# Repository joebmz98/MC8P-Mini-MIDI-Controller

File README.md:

# MC8P Mini MIDI Controller

---

# **8-Pot Mini MIDI Controller**

A compact, open-source MIDI controller with **8 potentiometers**, each with **fully assignable MIDI CCs**, built for **Arduino NANO R3/R4 (Rev1)** or the **Pro Micro (Rev2)**.

---

## **Features**
- **8x Potentiometers** with smooth analog control via 16-channel MUX
- **Arduino NANO / Pro Micro (Rev2) Compatible** – Easy to source and program
- **SSD1306 I2C OLED (128x64)** for the UI
- **Per-Pot CC Assignment** – Full MIDI CC customization
- **4x Tactile Switches** for UI navigation/configuration
- **Standalone Operation** – No computer needed after setup
- **EEPROM Settings Storage** – Retains configurations after power-off
- **Temporary Override Mode** – Make temporary adjustments that snap back
- **MIDI over USB** (Pro Micro Rev ONLY) – Class-compliant, plug-and-play
- **Open-Source Firmware** (Arduino IDE-compatible)

---

## **Bill of Materials (BOM)**

| Component                  | Qty | Notes                          | Links / Part Numbers |
|----------------------------|-----|--------------------------------|----------------------|
| Arduino NANO / Pro Micro   | 1   | Main microcontroller           | [Arduino NANO R3](https://www.aliexpress.com/w/wholesale-arduino-nano.html?spm=a2g0o.productlist.search.0) / [Pro Micro](https://www.aliexpress.com/w/wholesale-pro-micro-arduino.html?spm=a2g0o.best.search.0) |
| 16-Channel MUX (74HC4067)  | 1   | For reading 8 potentiometers   | [AliExpress](https://www.aliexpress.com/w/wholesale-cd74hc4067.html?spm=a2g0o.productlist.search.0) / CD74HC4067M96 (JLCPCB) |
| SSD1306 OLED (128×64)      | 1   | I²C interface                  | [AliExpress](https://www.aliexpress.com/w/wholesale-ssd1306.html?spm=a2g0o.productlist.search.0) |
| B100K Potentiometers       | 8   | Linear taper                   | [AliExpress](https://www.aliexpress.com/item/1005003523799166.html?spm=a2g0o.productlist.main.4.41b16412N16EC4&aem_p4p_detail=2026050202175910656752474918880005794025&algo_pvid=bb6ca2a0-bb84-4b86-8104-57e7c6a92d56&algo_exp_id=bb6ca2a0-bb84-4b86-8104-57e7c6a92d56-3&pdp_ext_f=%7B"order"%3A"368"%2C"eval"%3A"1"%2C"fromPage"%3A"search"%7D&pdp_npi=6%40dis%21GBP%210.33%210.33%21%21%210.43%210.43%21%402151e6dc17777134792648341e4c8f%2112000026166615223%21sea%21UK%216042796089%21X%211%210%21n_tag%3A-29919%3Bd%3A582ad943%3Bm03_new_user%3A-29895&curPageLogUid=hZYrDWLC06u8&utparam-url=scene%3Asearch%7Cquery_from%3A%7Cx_object_id%3A1005003523799166%7C_p_origin_prod%3A&search_p4p_id=2026050202175910656752474918880005794025_1) |
| Tactile Switches           | 4   | For menu navigation (ASSIGN, ENTER, PREV, NEXT) | K2-6639DP-B4SW-04 (JLCPCB) |
| 10k Resistors (SMD)        | 7   | Button pull-downs (R3–R6), MUX enable pull-down (R7), MIDI jumpers (R8, R9) | 0603WAF1002T5E (JLCPCB) |
| 100nF SMD Capacitor        | 1   | Power rail stabilisation       | 1206B104K101CT (JLCPCB) |
| 10nF SMD Capacitors        | 8   | Potentiometer filtering        | 1206B103K500NT (JLCPCB) |
| 220Ω SMD Resistors         | 2   | For MIDI circuitry             | 0603WAF2200T5E (JLCPCB) |
| PJ307 Stereo Headphone Socket | 1 | 3.5mm MIDI TRS Out (Type A) | — |
| Reset Button (SMD)         | 1   | Rev2 only - Reset button       | KMR221GLFS (JLCPCB) |
| 0.1" Header Pins           | 1   | For connecting components      | — |
| PCB                        | 1   | Custom design                  | — |
| Potentiometer Knobs        | 8   | For B100K potentiometers       | — |

---

## **Available Purchase Options**
**DIY Kits** - Only NANO version (rev1) available → [**Purchase from my Tindie store**](https://www.tindie.com/stores/axsinstruments/)

---

## **Installation & Setup**
### **1. Flashing the Firmware**
- Install **Arduino IDE**
- Install required libraries (see Building from Source section)
- Open the `.ino` file in Arduino IDE | There are two files - one for NANO and one for Pro Micro
- Select your board (**Arduino NANO R3/R4 or ProMicro**)
- Upload the firmware

### **2. Hardware Assembly**
- Refer to the *Build Guide* (coming soon)

### **3. First Boot**
- Power via **USB** on the Arduino NANO
- Use the **OLED menu** to assign CCs

---

## **Configuration**

### Button Functions

| Button | Primary Function |
|--------|-----------------|
| ASSIGN | Enter/exit MIDI assignment menu |
| ENTER | Enter temporary override mode (hold), confirm selections |
| PREV | Decrease values, navigate up |
| NEXT | Increase values, navigate down |
| PREV + NEXT (hold 2 sec) | Factory reset |

### Screen Hierarchy

The interface is organized into two main screens:

**MAIN SCREEN** → **ASSIGN SCREEN** → parameter editing

### Main Screen

This is your default operating view. The screen displays:
- Current selected pot number (1-8)
- A horizontal bar graph showing the current MIDI value (0-127)
- The numeric MIDI value centered on screen

From the main screen:
- Press **ASSIGN** to enter the assign menu
- Press and hold **ENTER** to activate temporary override mode

### Temporary Override Mode

When you press and hold ENTER on the main screen, the controller enters temporary override mode:
- The display inverts as visual feedback
- All potentiometer adjustments override the stored values
- When you release ENTER, the controller:
  - Returns to the stored MIDI values
  - Activates catch-up mode
  - The display returns to normal

### Catch-Up Mode

After exiting temporary override mode, catch-up mode is activated:
- Potentiometers must pass through their stored position before taking control
- This prevents abrupt jumps in your MIDI parameters
- Each pot is caught up on its own – a pot only needs to reach or cross its stored value, and pots you didn't touch stay live (NANO firmware v1.1)

### Assign Screen (MIDI ASSIGN)

Press ASSIGN from the main screen to enter the configuration menu. Press ENTER to step through the edit modes:

**Navigation flow:**
1. **SELECT POT** – Choose which pot (1-8) to configure
2. **EDIT CHANNEL** – Set MIDI channel (1-16) or OMNI
3. **EDIT CC** – Set Control Change number (0-127)
4. **EDIT MIN** – Minimum output value (0-127)
5. **EDIT MAX** – Maximum output value (0-127)
6. **EDIT DIR** – Normal (0-127) or Inverted (127-0)

**Editing values:**
- **PREV/NEXT** – Adjust values incrementally
- **Potentiometer 8** – Smooth continuous adjustment across full range - faster when selecting MIDI CC's and custom ranges. It only takes over once you turn it, so entering a mode doesn't overwrite the current value (NANO firmware v1.1)
- **ENTER** – Cycle through edit modes
- **ASSIGN** – Save settings and return to main screen

### Factory Reset

From the main screen, press and hold **PREV + NEXT** for 2 seconds:
- All settings reset to defaults
- Device confirms reset on screen
- Resets to:
  - Channel 1-8 (one per pot)
  - CC 7 for all pots
  - Min 0, Max 127
  - Normal direction

---

## **MIDI Implementation**
- **USB MIDI** – Class-compliant in rev2, no drivers needed
- **Per-Pot Configuration** – Each pot has independent:
  - MIDI Channel (1-16 or OMNI)
  - CC Number (0-127)
  - Value Range (min/max 0-127)
  - Direction (Normal/Inverted)
- **EEPROM Storage** – Settings persist after power-off

---

## **Building from Source**
- Requires **Arduino IDE**
- Libraries:
  - `Adafruit_SSD1306` – OLED display driver
  - `Adafruit_GFX` – Graphics library for UI
  - `MIDI` – MIDI protocol handling
  - `EEPROM` – Settings storage (built-in)
- NANO R3: Arduino AVR Boards core **1.8.3 or newer** (needed for the I2C bus timeout that stops a glitched OLED bus from freezing the controller)
- NANO firmware v1.1 shows the free RAM in the top-left of the boot screen. Below ~250 bytes the NANO is at risk of stack overflow – the OLED buffer alone takes 1 KB of its 2 KB

### **Simulating in Wokwi**
- Set `#define WOKWI 1` at the top of the NANO firmware before simulating. Wokwi's CD74HC4067 model takes up to a couple of milliseconds to follow a channel change, so with the normal 20 µs settle time every pot appears to move with whichever pot you turn. Set it back to `0` for real hardware.
- Wire each button as on the PCB: one side to 5V, the other to the input pin with a 10k resistor to GND.
- Tie the MUX `EN` pin to GND.
- The serial monitor shows raw MIDI bytes, not text – e.g. `°` `±` `²` are 0xB0–0xB2, Control Change on channels 1–3.

---

## **Hardware Pin Connections**

| Component      | Arduino NANO (Rev1) | Pro Micro (Rev2) |
|----------------|---------------------|------------------|
| MUX SIG        | A0                  | A0               |
| MUX S0         | D6                  | D8               |
| MUX S1         | D7                  | D9               |
| MUX S2         | D8                  | D10              |
| MUX S3         | D9                  | D16              |
| ASSIGN Button  | D2                  | D4               |
| ENTER Button   | D3                  | D5               |
| PREV Button    | D4                  | D6               |
| NEXT Button    | D5                  | D7               |
| OLED SDA       | A4 (SDA)            | D2 (SDA)         |
| OLED SCL       | A5 (SCL)            | D3 (SCL)         |
| MIDI TRS Out   | D1 (TX)             | D1 (TX)          |
| Pot 1-8        | MUX Channels 0-7    | MUX Channels 0-7 |

**Buttons are active-HIGH.** Each switch connects its pin to 5V, with a 10k pull-down to GND (R3–R6), so a pin reads **HIGH when pressed** and LOW when released. Use `INPUT`, not `INPUT_PULLUP` – the internal pull-up fights the external pull-down and leaves the idle level around 0.8–1.7 V, right at the AVR's LOW threshold. NANO firmware v1.1 uses `INPUT`; the Pro Micro firmware (v1.0) still enables the pull-up.

---

## **Differences from MC8P**

| Feature           | MC8P (Teensy 4.0)    | MC8P mini (Arduino)      |
|-------------------|----------------------|---------------------------|
| Microcontroller   | Teensy 4.0           | Arduino NANO / Pro Micro  |
| MIDI Output       | USB + TRS 3.5mm      | Rev1 TRS Only / Rev2 USB + TRS 3.5mm |
| Max CCs per Pot   | Up to 10             | 1                         |
| EEPROM            | Yes                  | Yes                       |
| Catch-up Mode     | Yes                  | Yes                       |
| Temp Override     | Yes                  | Yes                       |

---

## **License**
**MIT License** – Open-source for personal & commercial use

---

## **Support & Contributions**
- **Issues:** Open a GitHub ticket
- **Custom Requests:** Start a thread in the discussions page or email: axs.instruments@gmail.com
- **Want to improve it?** PRs welcome!

---

## **Version History**
- **v1.1** (NANO firmware) – Stability & performance
  - Fixes freezes: I2C bus timeout with automatic OLED recovery
  - Catch-up is per pot – no more pots locking up after temp mode, or MIDI/OLED flooding while waiting
  - OLED redraws batched and capped at ~25 fps (each redraw is a full 1 KB I2C transfer)
  - Full 0–127 resolution with no jitter (raw-domain hysteresis replaces the change-of-2 threshold)
  - Per-button debounce; buttons read as active-HIGH with `INPUT` to match the board's pull-downs
  - Faster ADC reads, ~120 bytes RAM saved from the MIDI library, free RAM on the boot screen
  - NANO R3 / R4 detected automatically – no lines to comment in/out
  - EEPROM layout unchanged – saved settings are kept when updating from v1.0
- **v1.0** – Initial release
  - 8-pot control via 74HC4067 MUX
  - Full MIDI CC assignment per pot
  - OLED UI with assign menu
  - EEPROM settings storage
  - Temporary override and catch-up modes
  - Factory reset function

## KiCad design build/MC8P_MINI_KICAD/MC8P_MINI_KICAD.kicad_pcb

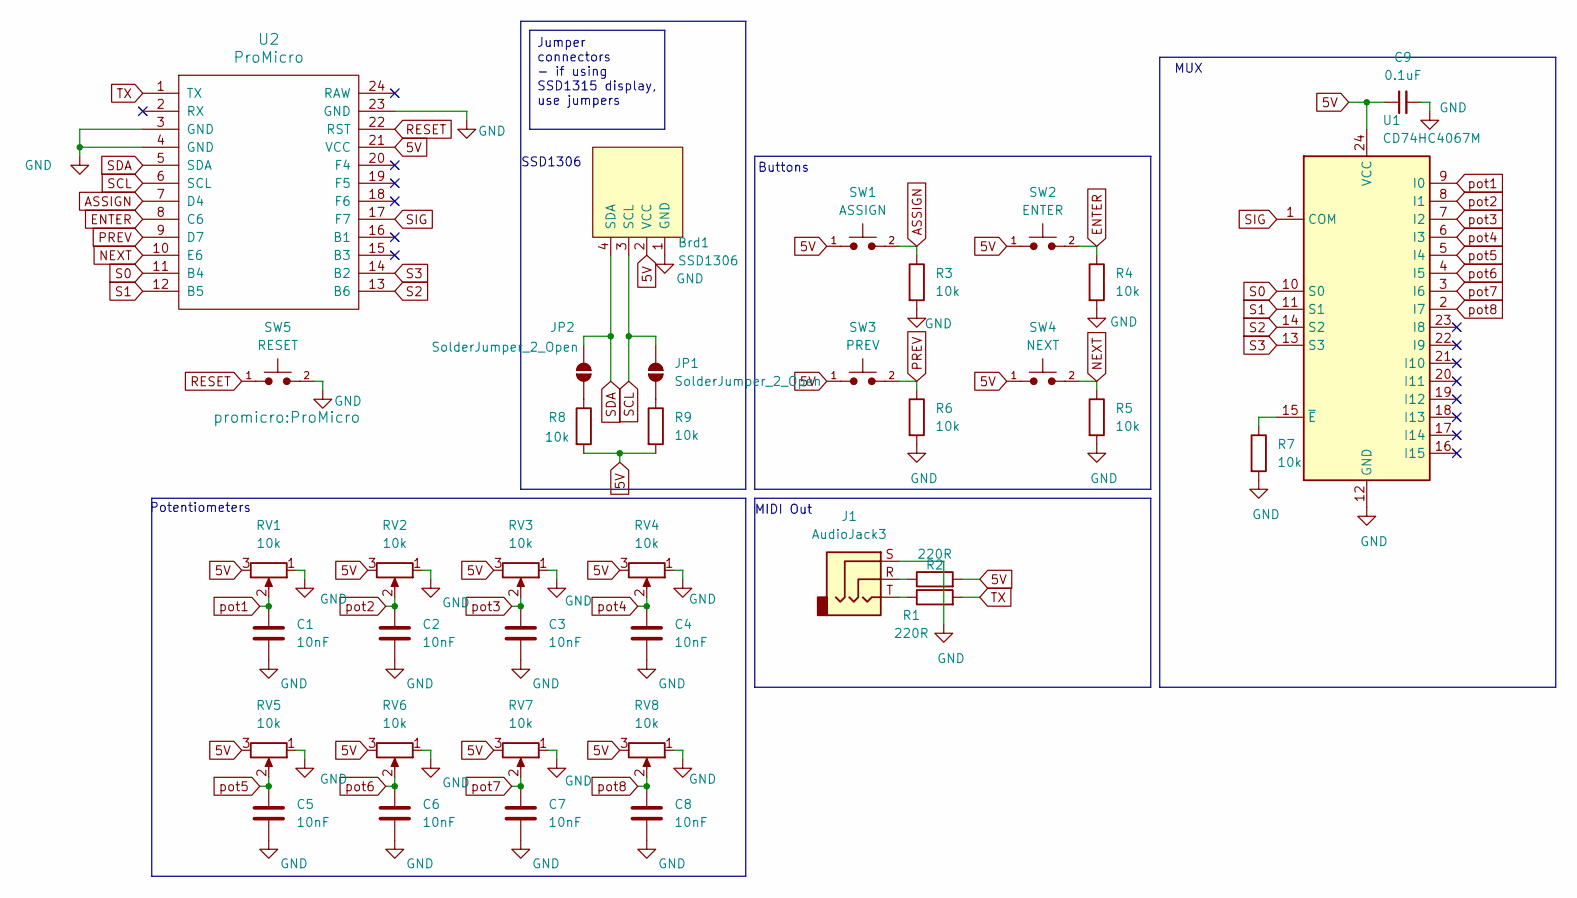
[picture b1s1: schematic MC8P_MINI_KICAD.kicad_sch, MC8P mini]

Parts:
Brd1: SSD1306; 128x64OLED
C1, C2, C3, C4, C5, C6, C7, C8: 10nF; C_1206_3216Metric
C9: 100nF_0603_16V; C_1206_3216Metric; Part Number 0603YC104KAT2A; JLCPCB ID C14663
J1: AudioJack3; Jack_3.5mm_CUI_SJ1-3525N_Horizontal
JP1, JP2: SolderJumper_2_Open; SolderJumper-2_P1.3mm_Open_RoundedPad1.0x1.5mm
R1, R2: 220R_0603; R_0603; Part Number RC0603FR-07220RL; JLCPCB ID C8218
R3, R4, R5, R6, R7, R8, R9: 10k_0402; R_0603; Part Number RT0402FRE0710KL
RV1, RV2, RV3, RV4, RV5, RV6, RV7, RV8: 10k; Potentiometer_RV09
SW1: ASSIGN; SW_PUSH_6mm
SW2: ENTER; SW_PUSH_6mm
SW3: PREV; SW_PUSH_6mm
SW4: NEXT; SW_PUSH_6mm
SW5: RESET; SW_Push_1P1T_NO_CK_KMR2
U1: CD74HC4067M; SOIC-24W_7.5x15.4mm_P1.27mm
U2: ProMicro

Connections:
5V: Brd1.2 (VCC), C9.1, R2.2, R8.2, R9.2, RV1.3, RV2.3, RV3.3, RV4.3, RV5.3, RV6.3, RV7.3, RV8.3, SW1.1, SW2.1, SW3.1, SW4.1, U1.24 (VCC), U2.21 (VCC)
ASSIGN: R3.1, SW1.2, U2.7 (D4)
ENTER: R4.1, SW2.2, U2.8 (C6)
GND: Brd1.1 (GND), C1.1, C2.1, C3.1, C4.1, C5.1, C6.1, C7.1, C8.1, C9.2, J1.S, R3.2, R4.2, R5.2, R6.2, R7.2, RV1.1, RV2.1, RV3.1, RV4.1, RV5.1, RV6.1, RV7.1, RV8.1, SW5.2, U1.12 (GND), U2.3 (GND), U2.4 (GND), U2.23 (GND)
NEXT: R5.1, SW4.2, U2.10 (E6)
unnamed: J1.R, R2.1
unnamed: J1.T, R1.1
unnamed: JP1.1 (A), R9.1
unnamed: JP2.1 (A), R8.1
unnamed: R7.1, U1.15 (~E)
PREV: R6.1, SW3.2, U2.9 (D7)
RESET: SW5.1, U2.22 (RST)
S0: U1.10 (S0), U2.11 (B4)
S1: U1.11 (S1), U2.12 (B5)
S2: U1.14 (S2), U2.13 (B6)
S3: U1.13 (S3), U2.14 (B2)
SCL: Brd1.3 (SCL), JP1.2 (B), U2.6 (SCL)
SDA: Brd1.4 (SDA), JP2.2 (B), U2.5 (SDA)
SIG: U1.1 (COM), U2.17 (F7)
TX: R1.2, U2.1 (TX)
pot1: C1.2, RV1.2, U1.9 (I0)
pot2: C2.2, RV2.2, U1.8 (I1)
pot3: C3.2, RV3.2, U1.7 (I2)
pot4: C4.2, RV4.2, U1.6 (I3)
pot5: C5.2, RV5.2, U1.5 (I4)
pot6: C6.2, RV6.2, U1.4 (I5)
pot7: C7.2, RV7.2, U1.3 (I6)
pot8: C8.2, RV8.2, U1.2 (I7)

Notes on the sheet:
MIDI Out
Potentiometers
Buttons
MUX
SSD1306
Jumper connectors - if using SSD1315 display, use jumpers

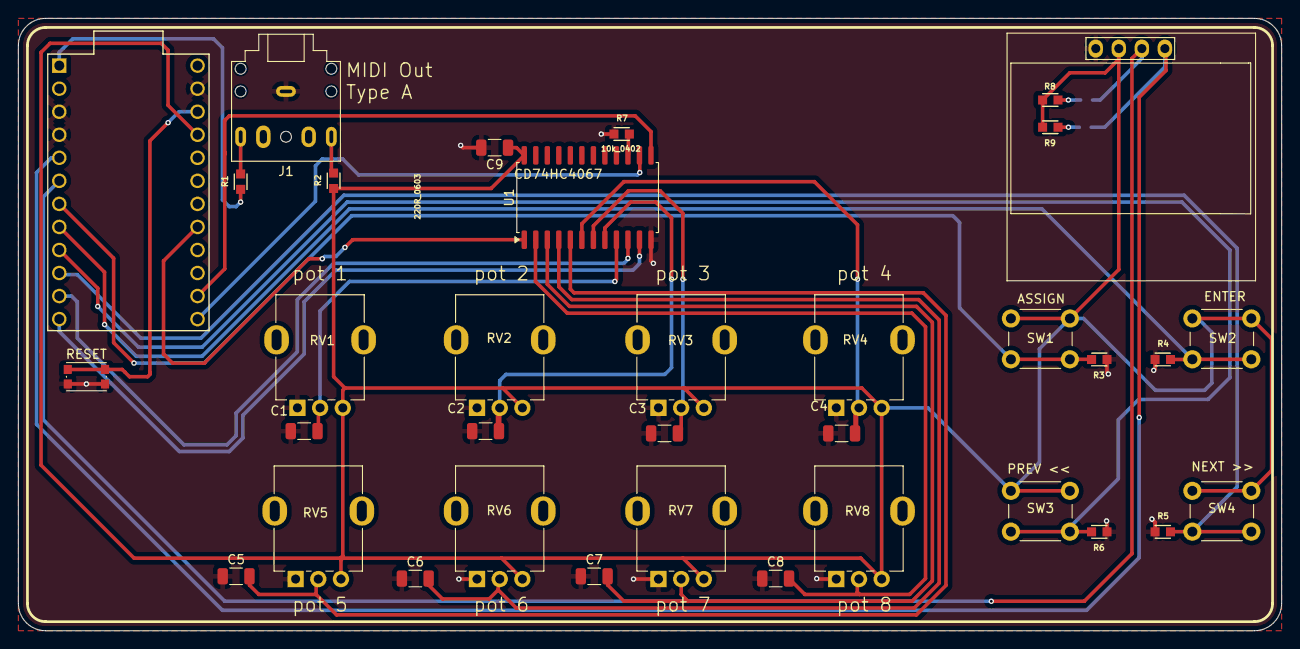
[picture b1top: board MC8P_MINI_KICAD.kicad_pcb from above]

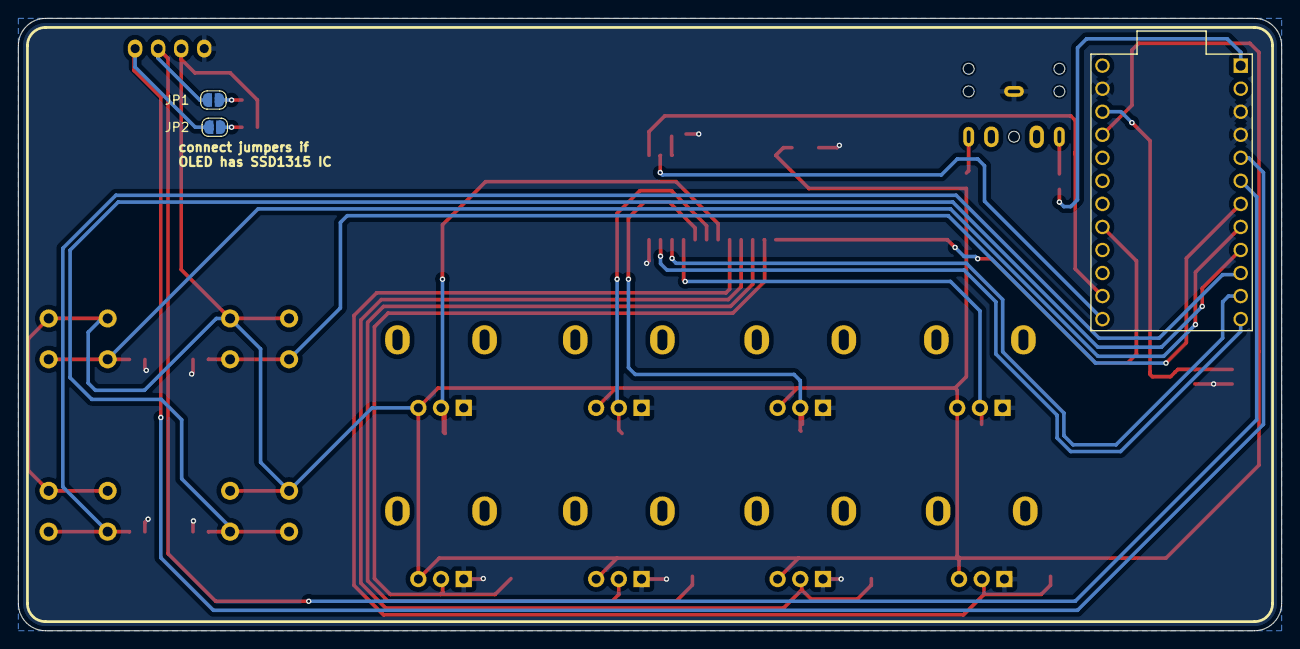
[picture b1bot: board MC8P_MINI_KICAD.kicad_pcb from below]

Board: 2 copper layers, 139.2 x 67.5 mm, 37 parts (2 on the bottom side), 28 nets.

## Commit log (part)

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2026-04-15 v1.0
2026-04-16 Moved strings to the flash memory
2026-04-16 production files
2026-04-16 temp mode
2026-04-17 integrated with r4
2026-04-17 MAIN_SCREEN update
2026-04-17 TEMP mode - catchup mode
2026-04-17 MIDI output fixed
    MIDI out for nano r4
2026-04-17 PCB & Schematic Updated
    Added pull up resistors with jumpers to work with Arduino nano r4
2026-04-18 UI edits
2026-04-18 PCB updated
    updated back side to indicate when jumper wires are used
2026-05-01 Optimisation
    optimised code for better functionality with NANO R3
2026-05-01 media
2026-05-01 added ProMicro version
    Created ProMicro version for USB MIDI support
2026-05-01 Pro Micro FW
    Added FW for Pro Micro Version
    - Adds USB MIDI
2026-05-02 PCV Rev2
    replaced Nano version with Pro Micro
2026-05-02 production files update
2026-05-04 USB MIDI Host detection
